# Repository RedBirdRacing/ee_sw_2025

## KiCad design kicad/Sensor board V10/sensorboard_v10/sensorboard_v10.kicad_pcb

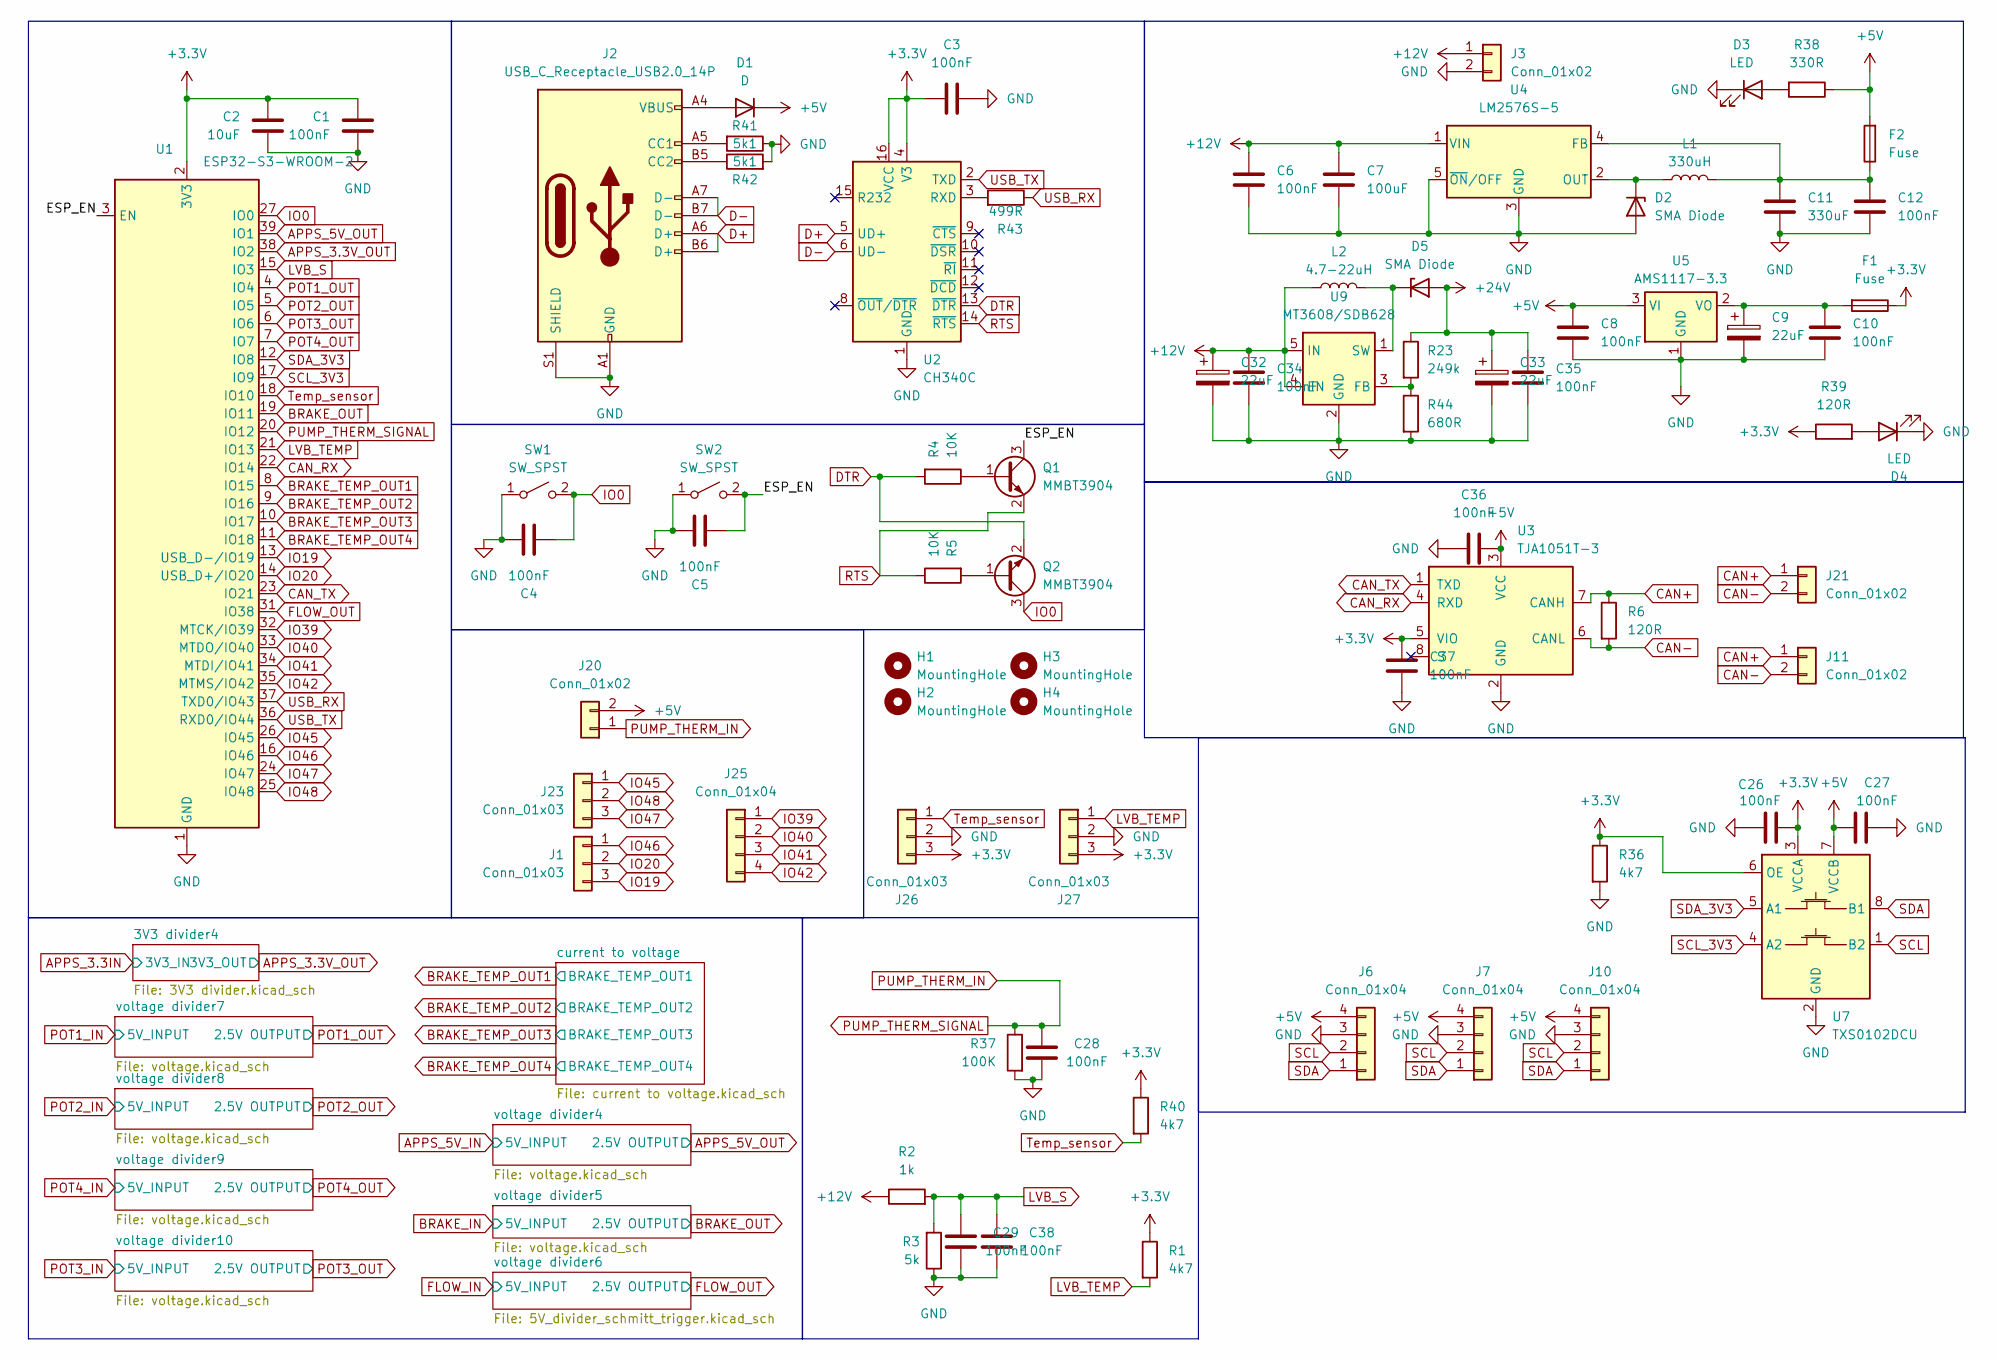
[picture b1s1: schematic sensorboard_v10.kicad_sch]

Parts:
C1, C3, C4, C5, C6, C8, C10, C12, C26, C27, C28, C29, C34, C35, C36, C37, C38: 100nF; C_0805_2012Metric_Pad1.18x1.45mm_HandSolder_L
C2: 10uF; C_0805_2012Metric_Pad1.18x1.45mm_HandSolder_L
C7: 100uF; CP_Radial_D6.3mm_P2.50mm
C9: 22uF; C_0805_2012Metric_Pad1.18x1.45mm_HandSolder_L
C11: 330uF; CP_Radial_D6.3mm_P2.50mm
C32, C33: 22uF; CP_EIA-3528-15_AVX-H_Pad1.50x2.35mm_HandSolder_RMC
D1: D; D_SMA_Handsoldering
D2, D5: SMA Diode; D_SMA_Handsoldering
D3, D4: LED; LED_0805_2012Metric_Pad1.45x1.40mm_HandSolder
F1, F2: Fuse; Fuse_1210_3225Metric_Pad1.42x2.65mm_HandSolder
H1, H2, H3, H4: MountingHole; MountingHole_3.2mm_M3
J1, J23, J26, J27: Conn_01x03; JST_XH_B3B-XH-A_1x03_P2.50mm_Vertical
J2: USB_C_Receptacle_USB2.0_14P; USB_C_Receptacle_G-Switch_GT-USB-7010ASV_Handsolder
J3: Conn_01x02; JST_VH_B2P-VH_1x02_P3.96mm_Vertical
J6, J7, J10, J25: Conn_01x04; JST_XH_B4B-XH-A_1x04_P2.50mm_Vertical
J11, J20, J21: Conn_01x02; JST_XH_B2B-XH-A_1x02_P2.50mm_Vertical
L1: 330uH; L_10.4x10.4_H4.8
L2: 4.7-22uH; L_Wuerth_HCI-5040
Q1, Q2: MMBT3904; SOT-23_Handsoldering
R1, R36, R40: 4k7; R_0805_2012Metric_Pad1.20x1.40mm_HandSolder_L
R2: 1k; R_0805_2012Metric_Pad1.20x1.40mm_HandSolder_L
R3: 5k; R_0805_2012Metric_Pad1.20x1.40mm_HandSolder_L
R4, R5: 10K; R_0805_2012Metric_Pad1.20x1.40mm_HandSolder_L
R6, R39: 120R; R_0805_2012Metric_Pad1.20x1.40mm_HandSolder_L
R23: 249k; R_0805_2012Metric_Pad1.20x1.40mm_HandSolder_L
R37: 100K; R_0805_2012Metric_Pad1.20x1.40mm_HandSolder_L
R38: 330R; R_0805_2012Metric_Pad1.20x1.40mm_HandSolder_L
R41, R42: 5k1; R_0805_2012Metric_Pad1.20x1.40mm_HandSolder_L
R43: 499R; R_0805_2012Metric_Pad1.20x1.40mm_HandSolder_L
R44: 680R; R_0805_2012Metric_Pad1.20x1.40mm_HandSolder_L
SW1, SW2: SW_SPST; SW_PUSH_6mm_H5mm
U1: ESP32-S3-WROOM-2; ESP32-WROOM-S3-2
U2: CH340C; SOIC-16_3.9x9.9mm_P1.27mm_Handsolder
U3: TJA1051T-3; SOIC-8_3.9x4.9mm_P1.27mm_RMC_Handsolder
U4: LM2576S-5; TO-263-5_TabPin3_Handsolder
U5: AMS1117-3.3; SOT-223-3_TabPin2_Handsolder
U7: TXS0102DCU; VSSOP-8_2.3x2mm_P0.5mm
U9: MT3608/SDB628; SOT-23-6_Handsoldering

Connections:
+3.3V: C1.2, C2.2, C3.2, C26.2, C37.2, F1.1, J26.3, J27.3, R1.1, R36.1, R39.1, R40.1, U1.2 (3V3), U2.4 (V3), U2.16 (VCC), U3.5 (VIO), U7.3 (VCCA), U7.6 (OE); also elsewhere on the board
+5V: C8.2, C27.1, C36.1, D1.1 (K), F2.2, J6.4, J7.4, J10.4, J20.2, R38.1, U3.3 (VCC), U5.3 (VI), U7.7 (VCCB); also elsewhere on the board
+12V: C6.2, C7.1, C32.1, C34.2, J3.1, L2.1, R2.1, U4.1 (VIN), U9.4 (EN), U9.5 (IN)
+24V: C33.1, C35.2, D5.2 (A), R23.1; also elsewhere on the board
/ESP_EN: C5.1, Q1.3 (C), SW2.2 (B), U1.3 (EN)
APPS_3.3V_OUT: U1.38 (IO2); also elsewhere on the board
APPS_5V_OUT: U1.39 (IO1); also elsewhere on the board
BRAKE_OUT: U1.19 (IO11); also elsewhere on the board
BRAKE_TEMP_OUT1: U1.8 (IO15); also elsewhere on the board
BRAKE_TEMP_OUT2: U1.9 (IO16); also elsewhere on the board
BRAKE_TEMP_OUT3: U1.10 (IO17); also elsewhere on the board
BRAKE_TEMP_OUT4: U1.11 (IO18); also elsewhere on the board
CAN+: J11.1, J21.1, R6.1, U3.7 (CANH)
CAN-: J11.2, J21.2, R6.2, U3.6 (CANL)
CAN_RX: U1.22 (IO14), U3.4 (RXD)
CAN_TX: U1.23 (IO21), U3.1 (TXD)
D+: J2.A6 (D+), J2.B6 (D+), U2.5 (UD+)
D-: J2.A7 (D-), J2.B7 (D-), U2.6 (UD-)
DTR: Q2.2 (E), R4.2, U2.13 (~DTR)
FLOW_OUT: U1.31 (IO38); also elsewhere on the board
GND: C1.1, C2.1, C3.1, C4.2, C5.2, C6.1, C7.2, C8.1, C9.2, C10.1, C11.2, C12.1, C26.1, C27.2, C28.2, C29.2, C32.2, C33.2, C34.1, C35.1, C36.2, C37.1, C38.2, D2.2 (A), D3.1 (K), D4.1 (K), J2.A1 (GND), J2.A12 (GND), J2.B1 (GND), J2.B12 (GND), J2.S1 (SHIELD), J3.2, J6.3, J7.3, J10.3, J26.2, J27.2, R3.1, R36.2, R37.2, R41.1, R42.2, R44.2, SW1.1 (A), SW2.1 (A), U1.1 (GND), U1.40 (GND), U1.41 (GND), U2.1 (GND), U3.2 (GND), U4.3 (GND), U4.5 (~ON/OFF), U5.1 (GND), U7.2 (GND), U9.2 (GND); also elsewhere on the board
IO0: C4.1, Q2.3 (C), SW1.2 (B), U1.27 (IO0)
IO19: J1.3, U1.13 (USB_D-/IO19)
IO20: J1.2, U1.14 (USB_D+/IO20)
IO39: J25.1, U1.32 (MTCK/IO39)
IO40: J25.2, U1.33 (MTDO/IO40)
IO41: J25.3, U1.34 (MTDI/IO41)
IO42: J25.4, U1.35 (MTMS/IO42)
IO45: J23.1, U1.26 (IO45)
IO46: J1.1, U1.16 (IO46)
IO47: J23.3, U1.24 (IO47)
IO48: J23.2, U1.25 (IO48)
LVB_S: C29.1, C38.1, R2.2, R3.2, U1.15 (IO3)
LVB_TEMP: J27.1, R1.2, U1.21 (IO13)
unnamed: D1.2 (A), J2.A4 (VBUS), J2.A9 (VBUS), J2.B4 (VBUS), J2.B9 (VBUS)
unnamed: D2.1 (K), L1.1, U4.2 (OUT)
unnamed: D3.2 (A), R38.2
unnamed: D4.2 (A), R39.2
unnamed: D5.1 (K), L2.2, U9.1 (SW)
unnamed: J2.A5 (CC1), R41.2
unnamed: J2.B5 (CC2), R42.1
unnamed: Q1.1 (B), R4.1
unnamed: Q2.1 (B), R5.2
unnamed: R43.2, U2.3 (RXD)
unnamed: C11.1, C12.2, F2.1, L1.2, U4.4 (FB)
unnamed: C9.1, C10.2, F1.2, U5.2 (VO)
unnamed: R23.2, R44.1, U9.3 (FB)
POT1_OUT: U1.4 (IO4); also elsewhere on the board
POT2_OUT: U1.5 (IO5); also elsewhere on the board
POT3_OUT: U1.6 (IO6); also elsewhere on the board
POT4_OUT: U1.7 (IO7); also elsewhere on the board
PUMP_THERM_IN: C28.1, J20.1, R37.1, U1.20 (IO12)
RTS: Q1.2 (E), R5.1, U2.14 (~RTS)
SCL: J6.2, J7.2, J10.2, U7.1 (B2)
SCL_3V3: U1.17 (IO9), U7.4 (A2)
SDA: J6.1, J7.1, J10.1, U7.8 (B1)
SDA_3V3: U1.12 (IO8), U7.5 (A1)
Temp_sensor: J26.1, R40.2, U1.18 (IO10)
USB_RX: R43.1, U1.37 (TXD0/IO43)
USB_TX: U1.36 (RXD0/IO44), U2.2 (TXD)

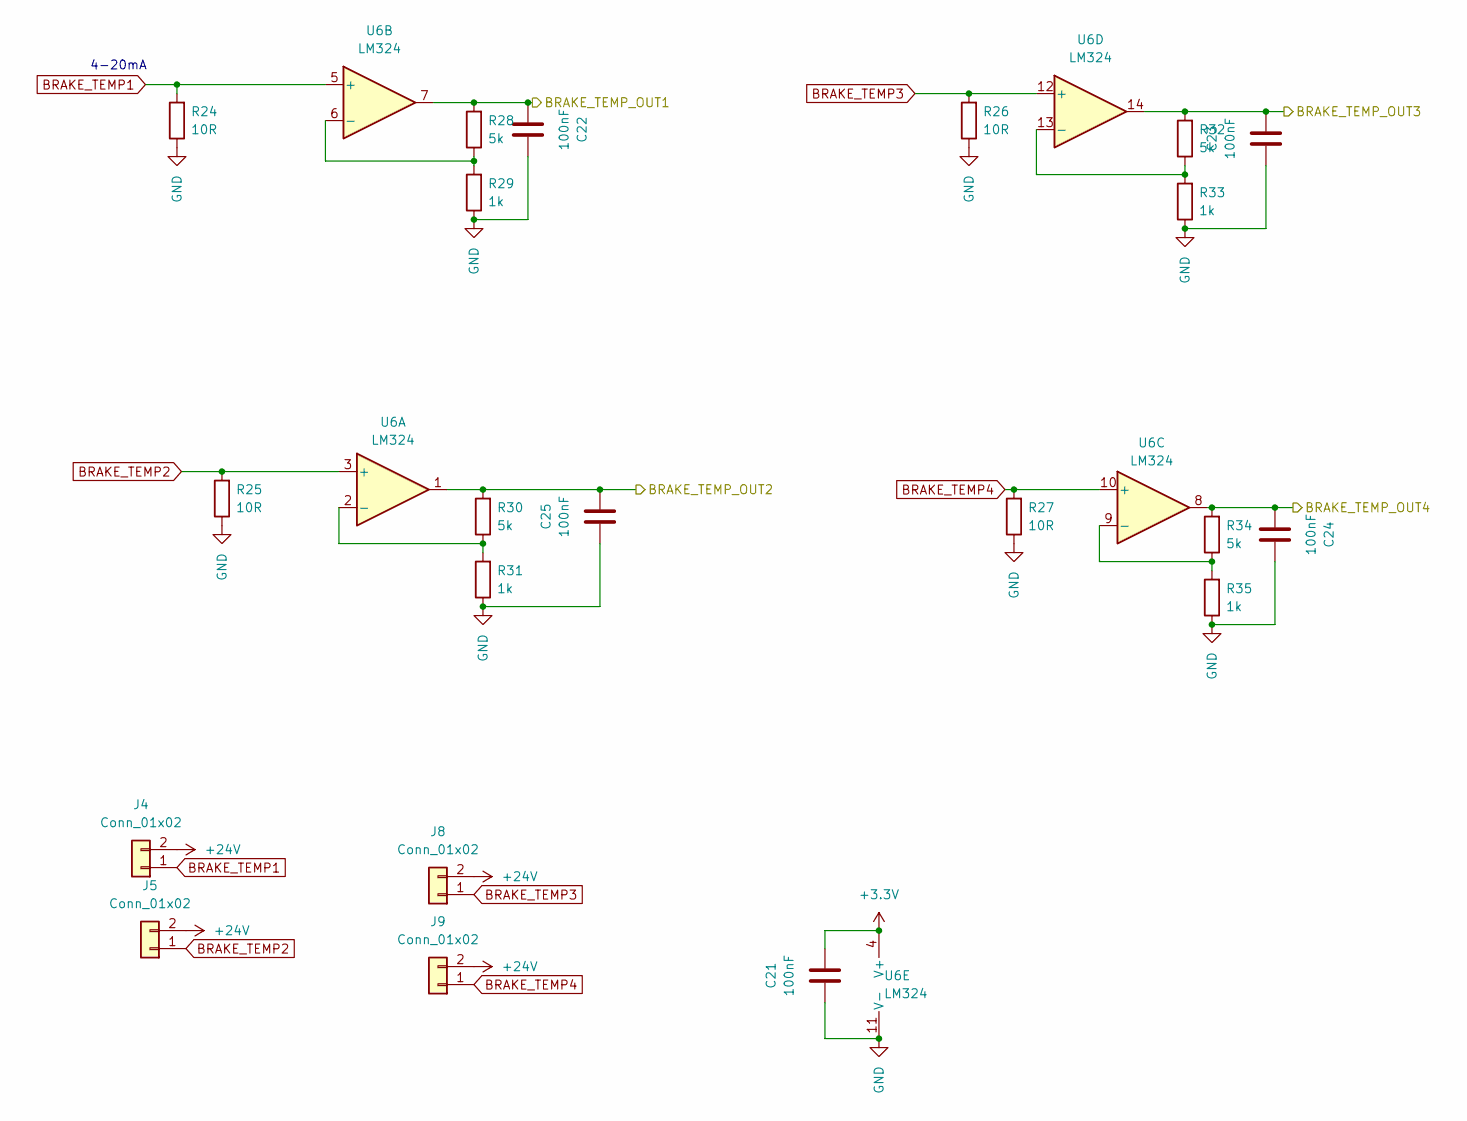
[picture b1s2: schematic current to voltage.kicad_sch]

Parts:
C21, C22, C23, C24, C25: 100nF; C_0805_2012Metric_Pad1.18x1.45mm_HandSolder_L
J4, J5, J8, J9: Conn_01x02; JST_XH_B2B-XH-A_1x02_P2.50mm_Vertical
R24, R25, R26, R27: 10R; R_1206_3216Metric_Pad1.30x1.75mm_HandSolder_RMC
R28, R30, R32, R34: 5k; R_0805_2012Metric_Pad1.20x1.40mm_HandSolder_L
R29, R31, R33, R35: 1k; R_0805_2012Metric_Pad1.20x1.40mm_HandSolder_L
U6: LM324; SOIC127P600X175-14N

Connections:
+3.3V: C21.1, U6.4 (V+); also elsewhere on the board
+24V: J4.2, J5.2, J8.2, J9.2; also elsewhere on the board
BRAKE_TEMP1: J4.1, R24.2, U6.5 (+)
BRAKE_TEMP2: J5.1, R25.2, U6.3 (+)
BRAKE_TEMP3: J8.1, R26.2, U6.12 (+)
BRAKE_TEMP4: J9.1, R27.2, U6.10 (+)
BRAKE_TEMP_OUT1: C22.1, R28.2, U6.7; also elsewhere on the board
BRAKE_TEMP_OUT2: C25.1, R30.2, U6.1; also elsewhere on the board
BRAKE_TEMP_OUT3: C23.1, R32.2, U6.14; also elsewhere on the board
BRAKE_TEMP_OUT4: C24.1, R34.2, U6.8; also elsewhere on the board
GND: C21.2, C22.2, C23.2, C24.2, C25.2, R24.1, R25.1, R26.1, R27.1, R29.1, R31.1, R33.1, R35.1, U6.11 (V-); also elsewhere on the board
unnamed: R30.1, R31.2, U6.2 (-)
unnamed: R28.1, R29.2, U6.6 (-)
unnamed: R34.1, R35.2, U6.9 (-)
unnamed: R32.1, R33.2, U6.13 (-)

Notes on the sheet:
4-20mA

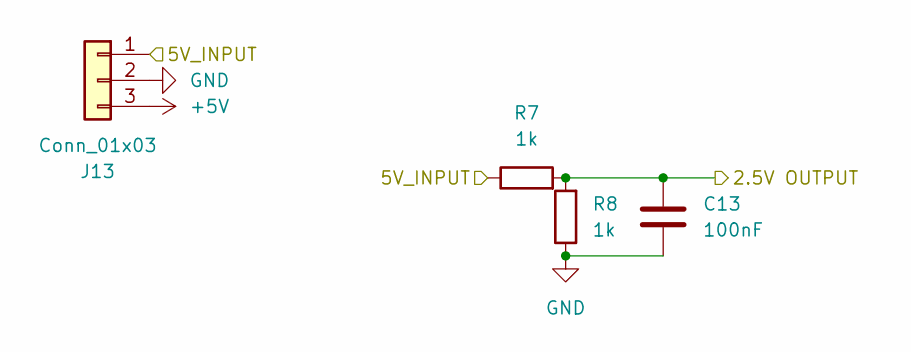
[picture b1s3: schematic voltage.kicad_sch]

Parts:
C13: 100nF; C_0805_2012Metric_Pad1.18x1.45mm_HandSolder_L
J13: Conn_01x03; JST_XH_B3B-XH-A_1x03_P2.50mm_Vertical
R7, R8: 1k; R_0805_2012Metric_Pad1.20x1.40mm_HandSolder_L

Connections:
+5V: J13.3; also elsewhere on the board
GND: C13.1, J13.2, R8.1; also elsewhere on the board
POT1_OUT: C13.2, R7.2, R8.2; also elsewhere on the board

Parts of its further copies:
C14, C15, C16, C17, C18: 100nF; C_0805_2012Metric_Pad1.18x1.45mm_HandSolder_L
J12, J14, J15, J16, J17: Conn_01x03; JST_XH_B3B-XH-A_1x03_P2.50mm_Vertical
R9, R10, R11, R12, R13, R14, R15, R16, R17, R18: 1k; R_0805_2012Metric_Pad1.20x1.40mm_HandSolder_L

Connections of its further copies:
+5V: J12.3, J14.3, J15.3, J16.3, J17.3; also elsewhere on the board
APPS_5V_IN: J16.1, R15.1
APPS_5V_OUT: C17.2, R15.2, R16.2; also elsewhere on the board
BRAKE_IN: J17.1, R17.1
BRAKE_OUT: C18.2, R17.2, R18.2; also elsewhere on the board
GND: C14.1, C15.1, C16.1, C17.1, C18.1, J12.2, J14.2, J15.2, J16.2, J17.2, R10.1, R12.1, R14.1, R16.1, R18.1; also elsewhere on the board
POT2_OUT: C14.2, R9.2, R10.2; also elsewhere on the board
POT3_IN: J15.1, R13.1
POT3_OUT: C16.2, R13.2, R14.2; also elsewhere on the board
POT4_IN: J14.1, R11.1
POT4_OUT: C15.2, R11.2, R12.2; also elsewhere on the board

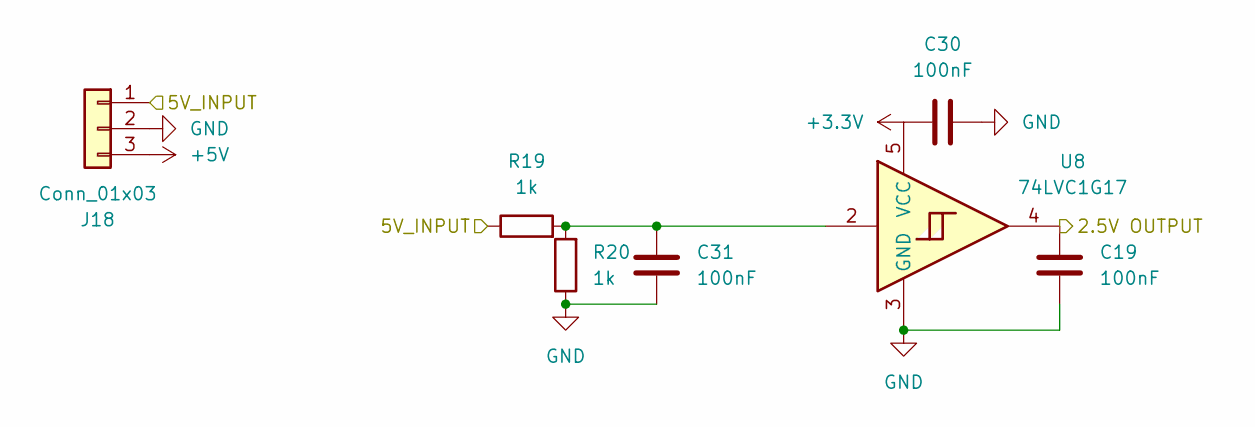
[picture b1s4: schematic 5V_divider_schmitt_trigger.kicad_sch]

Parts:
C19, C30, C31: 100nF; C_0805_2012Metric_Pad1.18x1.45mm_HandSolder_L
J18: Conn_01x03; JST_XH_B3B-XH-A_1x03_P2.50mm_Vertical
R19, R20: 1k; R_0805_2012Metric_Pad1.20x1.40mm_HandSolder_L
U8: 74LVC1G17; SOT-23-5_HandSoldering

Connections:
+3.3V: C30.2, U8.5 (VCC); also elsewhere on the board
+5V: J18.3; also elsewhere on the board
FLOW_IN: J18.1, R19.1
FLOW_OUT: C19.2, U8.4; also elsewhere on the board
GND: C19.1, C30.1, C31.1, J18.2, R20.1, U8.3 (GND); also elsewhere on the board
unnamed: C31.2, R19.2, R20.2, U8.2

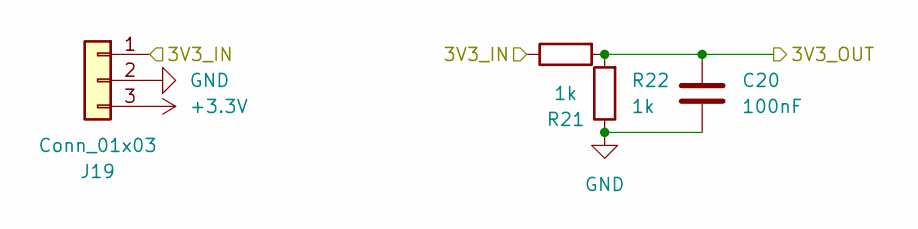
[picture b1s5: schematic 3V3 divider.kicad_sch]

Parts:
C20: 100nF; C_0805_2012Metric_Pad1.18x1.45mm_HandSolder_L
J19: Conn_01x03; JST_XH_B3B-XH-A_1x03_P2.50mm_Vertical
R21, R22: 1k; R_0805_2012Metric_Pad1.20x1.40mm_HandSolder_L

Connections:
+3.3V: J19.3; also elsewhere on the board
APPS_3.3IN: J19.1, R21.1
APPS_3.3V_OUT: C20.2, R21.2, R22.2; also elsewhere on the board
GND: C20.1, J19.2, R22.1; also elsewhere on the board

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
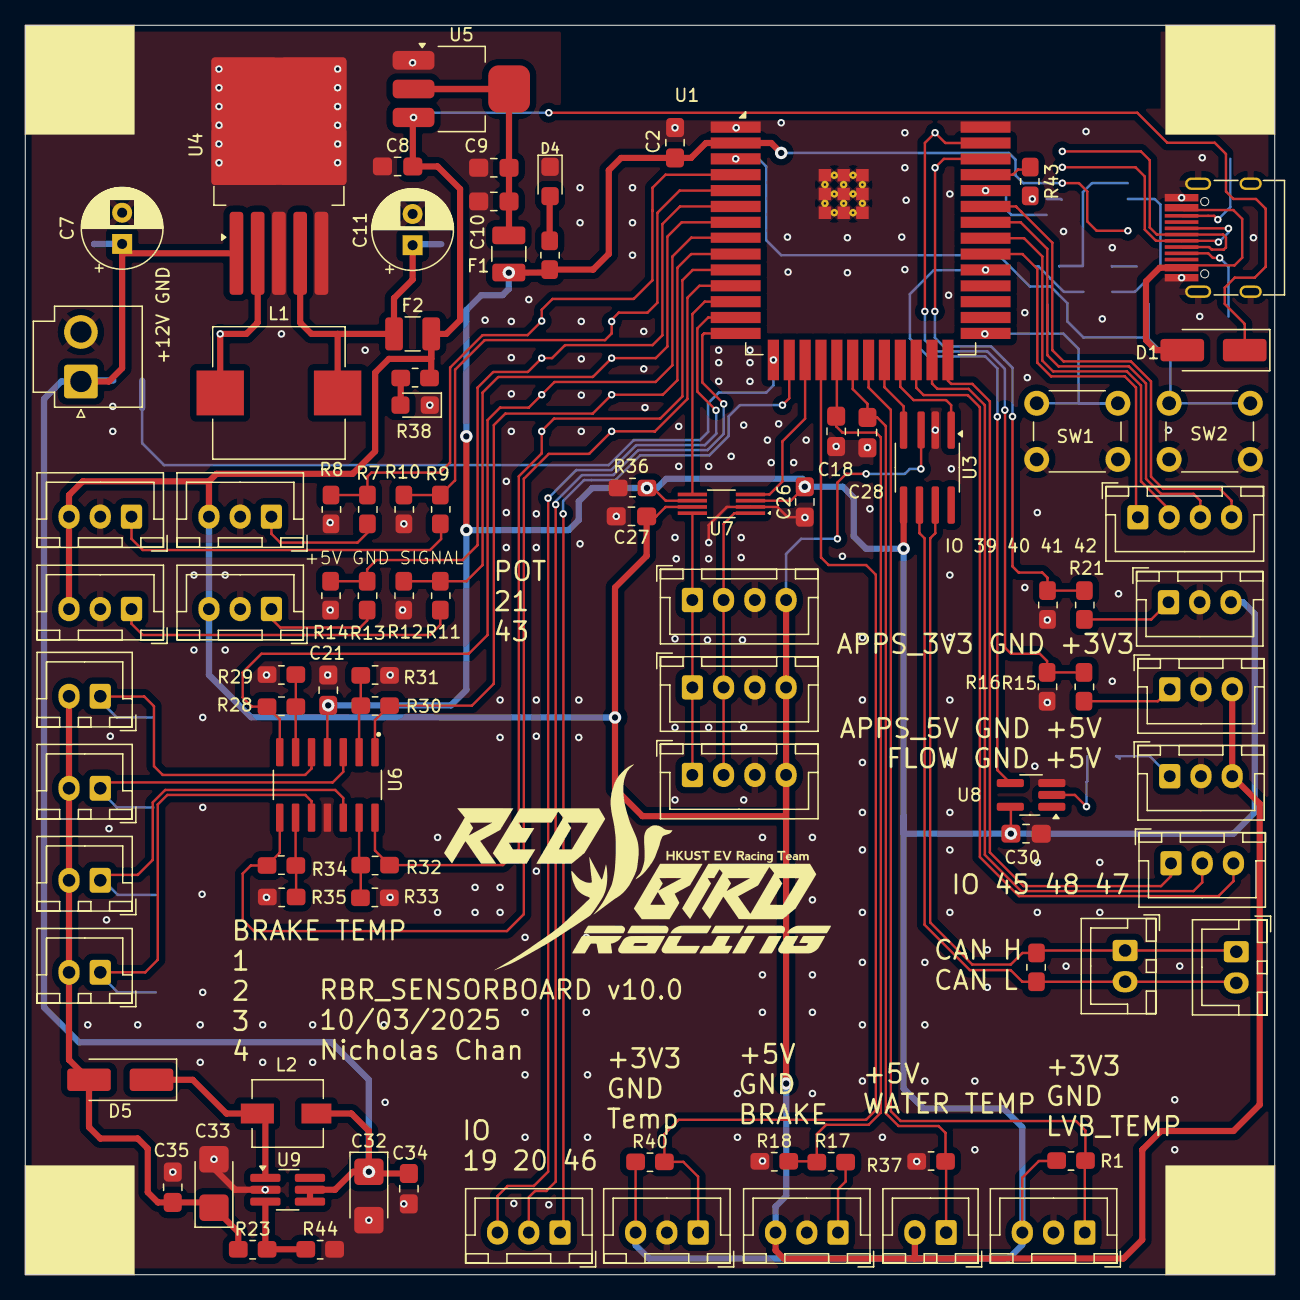
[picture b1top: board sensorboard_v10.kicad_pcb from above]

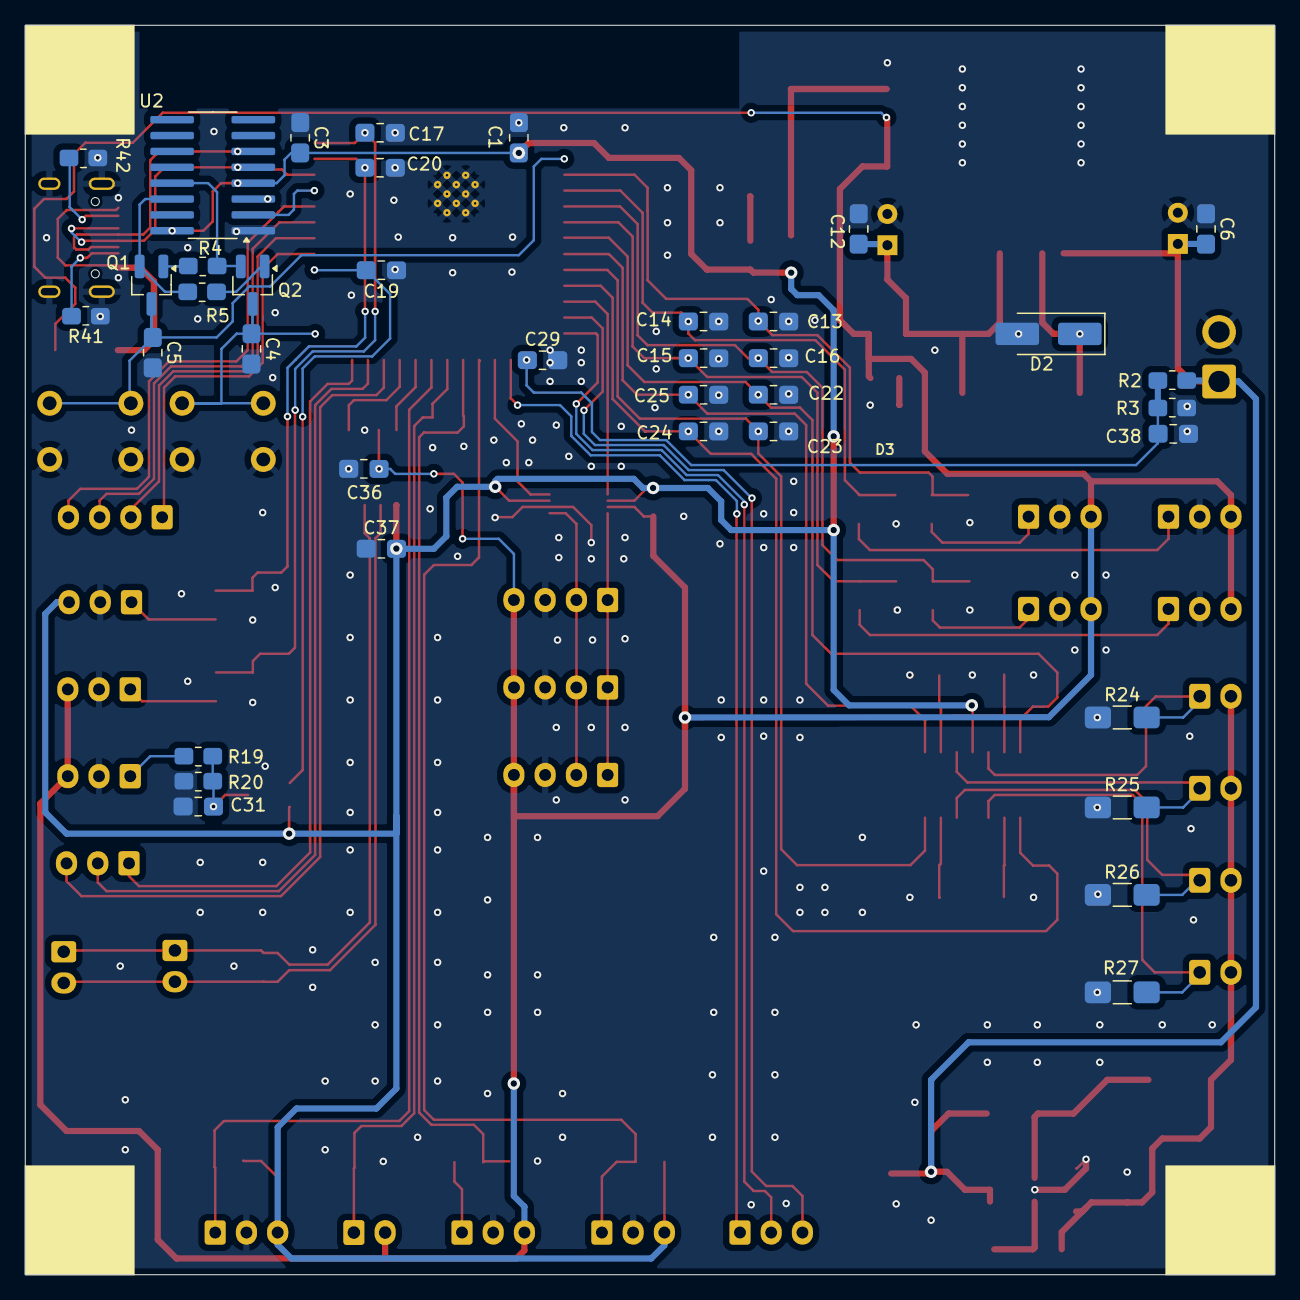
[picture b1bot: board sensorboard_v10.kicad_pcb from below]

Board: 2 copper layers, 100.0 x 100.0 mm, 133 parts (38 on the bottom side), 77 nets.

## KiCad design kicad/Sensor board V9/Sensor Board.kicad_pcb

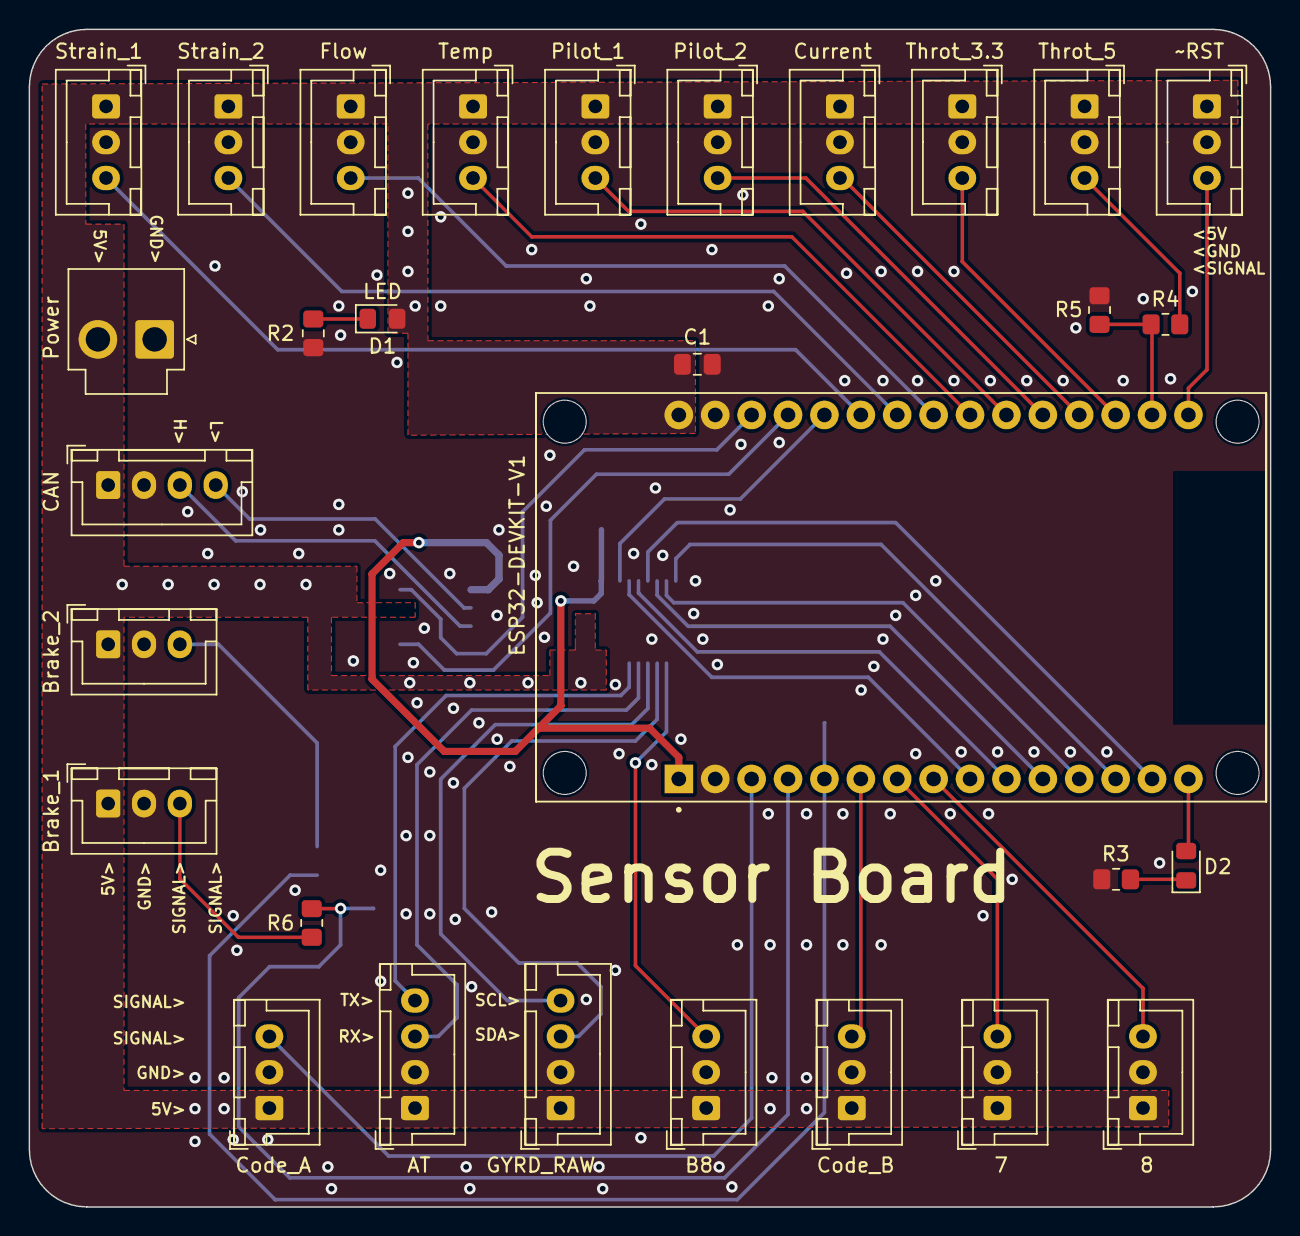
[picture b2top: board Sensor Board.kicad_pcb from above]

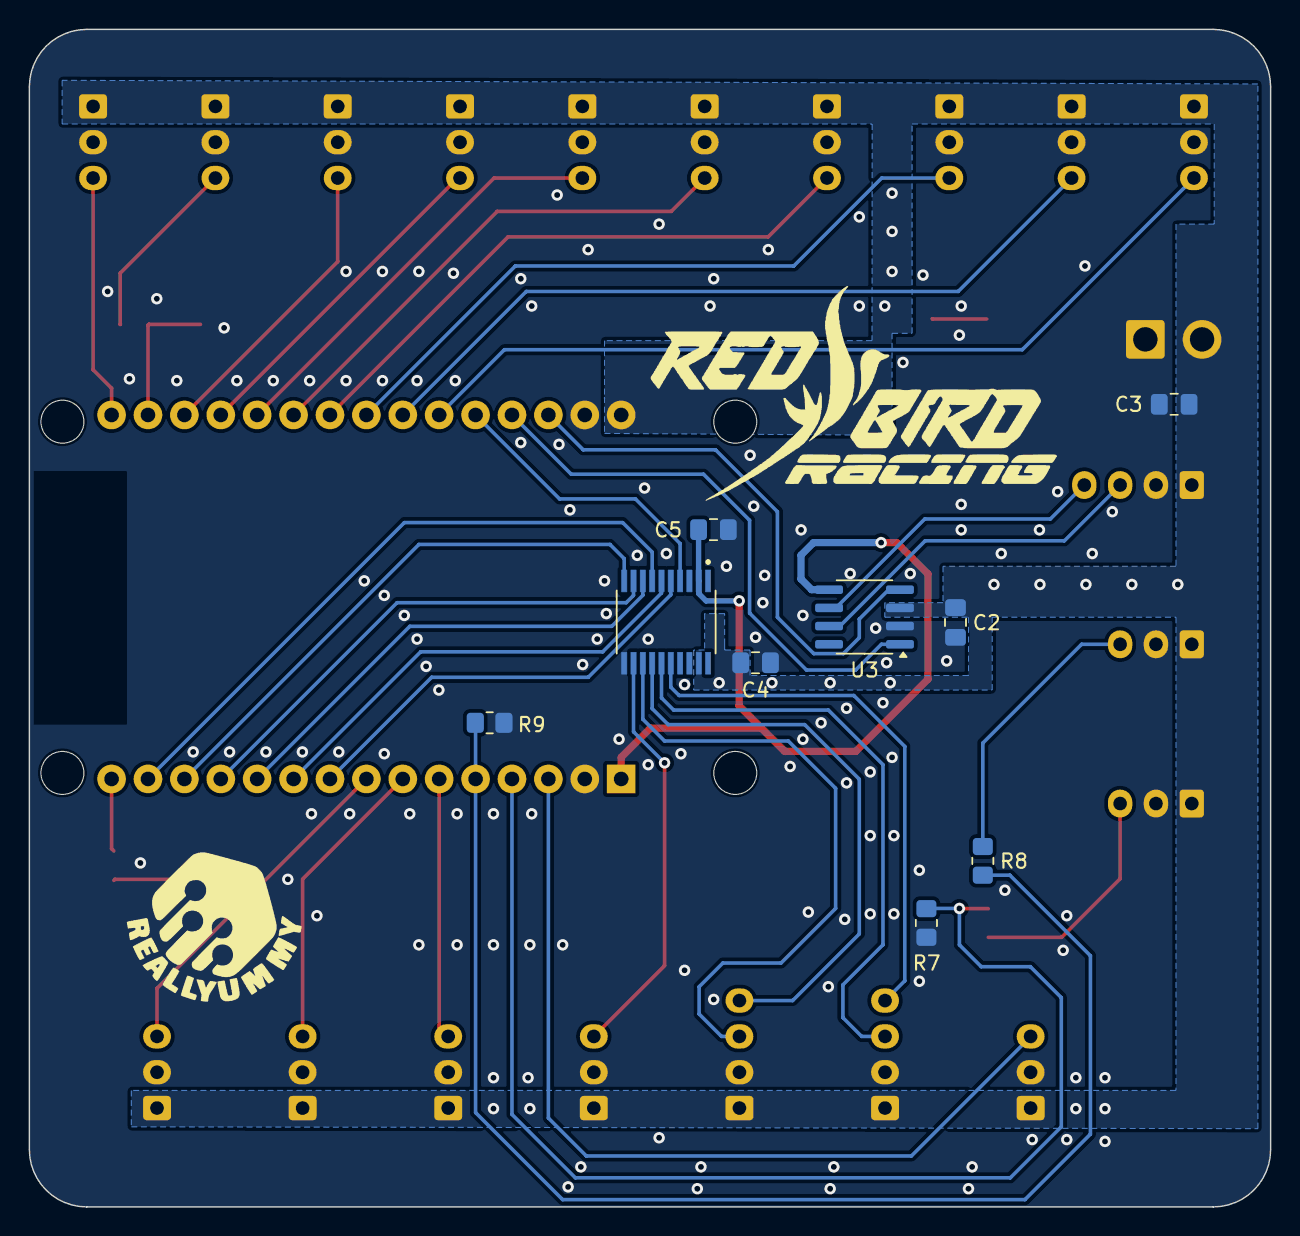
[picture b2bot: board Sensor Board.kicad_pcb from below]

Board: 2 copper layers, 86.6 x 82.2 mm, 38 parts (9 on the bottom side), 40 nets.

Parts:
7, 8: Conn_01x03_Pin; JST_XH_B3B-XH-A_1x03_P2.50mm_Vertical
AT: Conn_01x04_Pin; JST_XH_B4B-XH-A_1x04_P2.50mm_Vertical
B8: Conn_01x03_Pin; JST_XH_B3B-XH-A_1x03_P2.50mm_Vertical
Brake_1, Brake_2: Conn_01x03_Pin; JST_XH_B3B-XH-A_1x03_P2.50mm_Vertical
C1: 10uF; C_0805_2012Metric_Pad1.18x1.45mm_HandSolder
C2, C3, C4, C5: 0.1uF; C_0805_2012Metric_Pad1.18x1.45mm_HandSolder
CAN: Conn_01x04_Pin; JST_XH_B4B-XH-A_1x04_P2.50mm_Vertical
Code_A: Conn_01x03_Pin; JST_XH_B3B-XH-A_1x03_P2.50mm_Vertical
Code_B: Conn_01x03_Pin; JST_XH_B3B-XH-A_1x03_P2.50mm_Vertical
Current: Conn_01x03_Pin; JST_XH_B3B-XH-A_1x03_P2.50mm_Vertical
D1, D2: LED; LED_0805_2012Metric_Pad1.15x1.40mm_HandSolder
Flow: Conn_01x03_Pin; JST_XH_B3B-XH-A_1x03_P2.50mm_Vertical
GYRD_RAW: Conn_01x04_Pin; JST_XH_B4B-XH-A_1x04_P2.50mm_Vertical
Pilot_1, Pilot_2: Conn_01x03_Pin; JST_XH_B3B-XH-A_1x03_P2.50mm_Vertical
Power: Conn_01x02_Male; JST_VH_B2P-VH_1x02_P3.96mm_Vertical
R2, R3: 1kR; R_0805_2012Metric_Pad1.20x1.40mm_HandSolder
R4, R5, R6, R7, R8, R9: R_Small_US; R_0805_2012Metric_Pad1.20x1.40mm_HandSolder
Strain_1, Strain_2: Conn_01x03_Pin; JST_XH_B3B-XH-A_1x03_P2.50mm_Vertical
Temp: Conn_01x03_Pin; JST_XH_B3B-XH-A_1x03_P2.50mm_Vertical
Throt_3.3, Throt_5: Conn_01x03_Pin; JST_XH_B3B-XH-A_1x03_P2.50mm_Vertical
U1: ESP32-DEVKIT-V1; MODULE_ESP32_DEVKIT_V1
U2: TXS0108EPW; SOP65P640X120-20N
U3: TJA1051T-3; SOIC-8_3.9x4.9mm_P1.27mm

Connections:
7: 7.3, U1.7 (TX2)
8: 8.3, U1.8 (D5)
+3.3V: C5.2, U1.1 (3V3), U2.2 (VCCA), U3.5 (VIO)
+5V: 7.1, 8.1, AT.1, B8.1, Brake_1.1, Brake_2.1, C1.1, C2.1, C3.1, C4.2, CAN.1, Code_A.1, Code_B.1, Current.1, D1.2 (A), Flow.1, GYRD_RAW.1, Pilot_1.1, Pilot_2.1, Power.2, Strain_1.1, Strain_2.1, Temp.1, Throt_3.3.1, Throt_5.1, U1.30 (VIN), U2.19 (VCCB), U3.3 (VCC)
A8: U1.12 (RX0), U2.9 (A8)
AT_RX: AT.3, U2.15 (B5)
AT_TX: AT.4, U2.16 (B4)
B8: B8.3, U2.12 (B8)
Brake-1: Brake_1.3, R6.1
Brake-1-S: R6.2, R7.1, U1.4 (D2)
Brake-2: Brake_2.3, R8.1
Brake-2-S: R8.2, R9.1, U1.5 (D4)
CANH: CAN.3, U3.7 (CANH)
CANL: CAN.4, U3.6 (CANL)
CAN_RX: U1.28 (D13), U3.4 (RXD)
CAN_TX: U1.27 (D12), U3.1 (TXD)
Code A: Code_A.3, U1.3 (D15)
Code B: Code_B.3, U1.6 (RX2)
Current: Current.3, U1.19 (D34)
Flow: Flow.3, U1.23 (D25)
GND: 7.2, 8.2, AT.2, B8.2, Brake_1.2, Brake_2.2, C1.2, C2.2, C3.2, C4.1, C5.1, CAN.2, Code_A.2, Code_B.2, Current.2, Flow.2, GYRD_RAW.2, Pilot_1.2, Pilot_2.2, Power.1, R2.1, R3.1, R5.2, R7.2, R9.2, Strain_1.2, Strain_2.2, Temp.2, Throt_3.3.2, Throt_5.2, U1.2 (GND), U1.29 (GND), U2.11 (GND), U3.2 (GND)
GYRO_SCL: U1.14 (D22), U2.7 (A6)
GYRO_SCL_RAW: GYRD_RAW.4, U2.14 (B6)
GYRO_SDA: U1.11 (D21), U2.8 (A7)
GYRO_SDA_RAW: GYRD_RAW.3, U2.13 (B7)
unnamed: D1.1 (K), R2.2
unnamed: D2.1 (K), R3.2
OE: U1.13 (TX0), U2.10 (OE)
Pitot_1: Pilot_1.3, U1.21 (D32)
Pitot_2: Pilot_2.3, U1.20 (D35)
RX: U1.10 (D19), U2.6 (A5)
SCK: U1.26 (D14), U2.4 (A3)
Status: D2.2 (A), U1.15 (D23)
Strain_1: Strain_1.3, U1.25 (D27)
Strain_2: Strain_2.3, U1.24 (D26)
TX: U1.9 (D18), U2.5 (A4)
Temp: Temp.3, U1.22 (D33)
Throttle_3.3: Throt_3.3.3, U1.18 (VN)
Throttle_5: R4.1, Throt_5.3
Throttle_5_S: R4.2, R5.1, U1.17 (VP)
